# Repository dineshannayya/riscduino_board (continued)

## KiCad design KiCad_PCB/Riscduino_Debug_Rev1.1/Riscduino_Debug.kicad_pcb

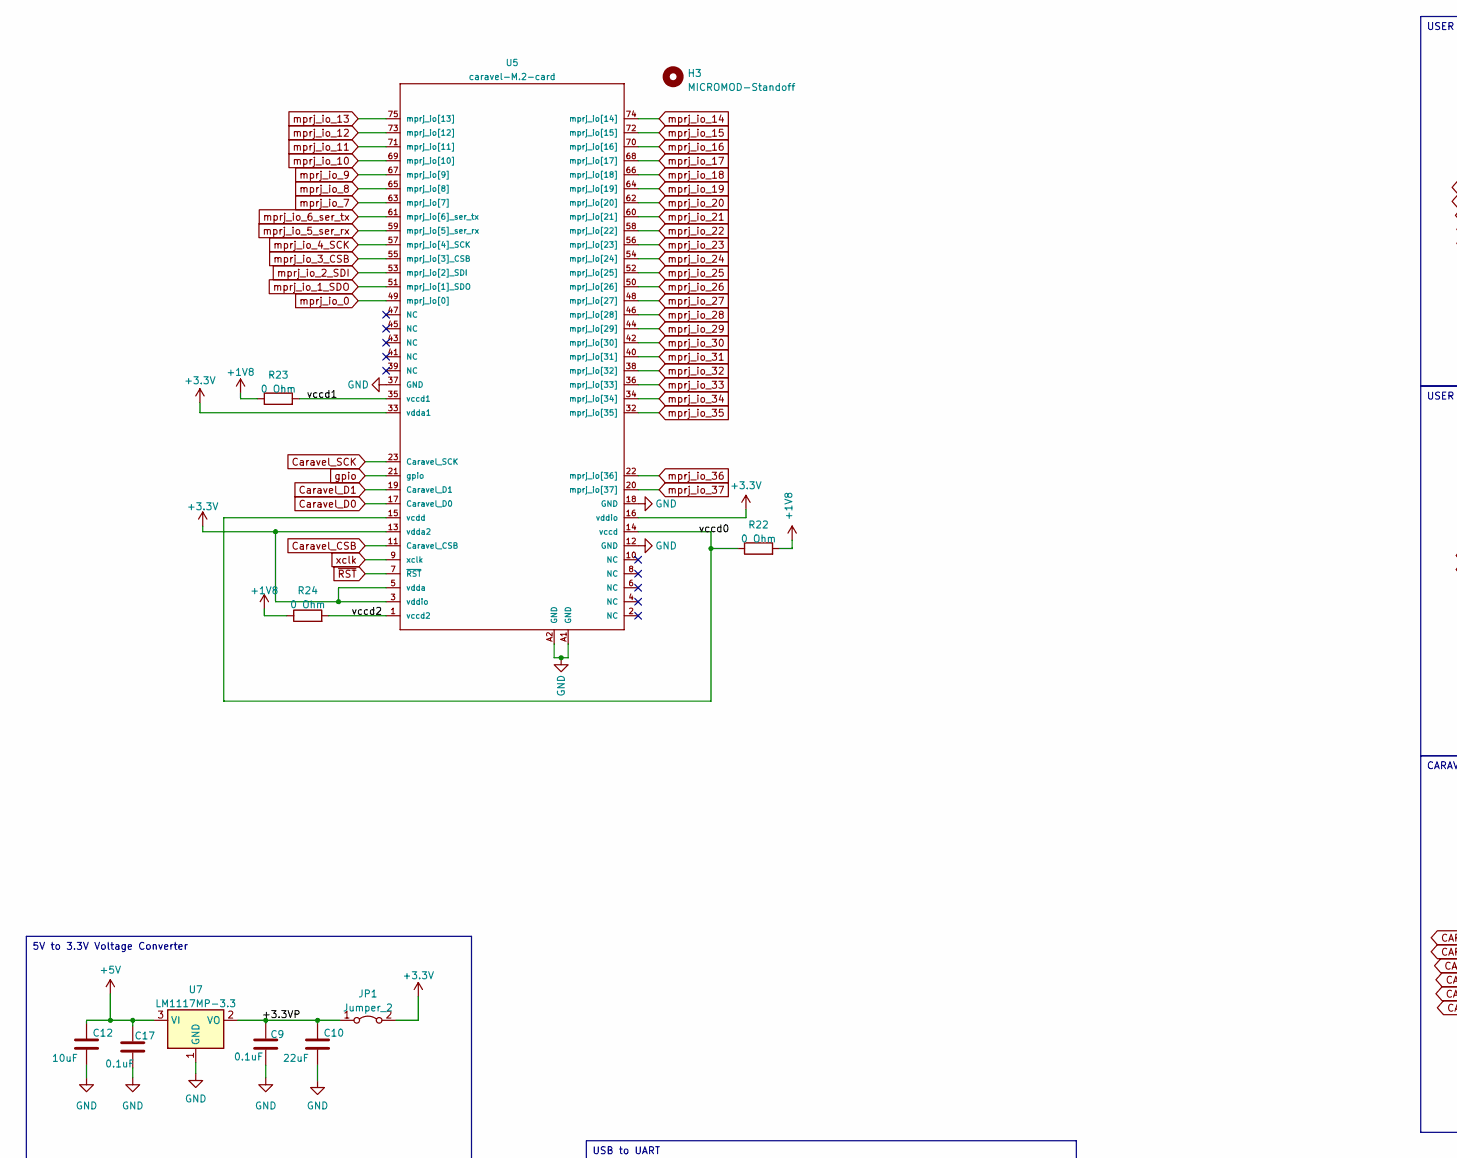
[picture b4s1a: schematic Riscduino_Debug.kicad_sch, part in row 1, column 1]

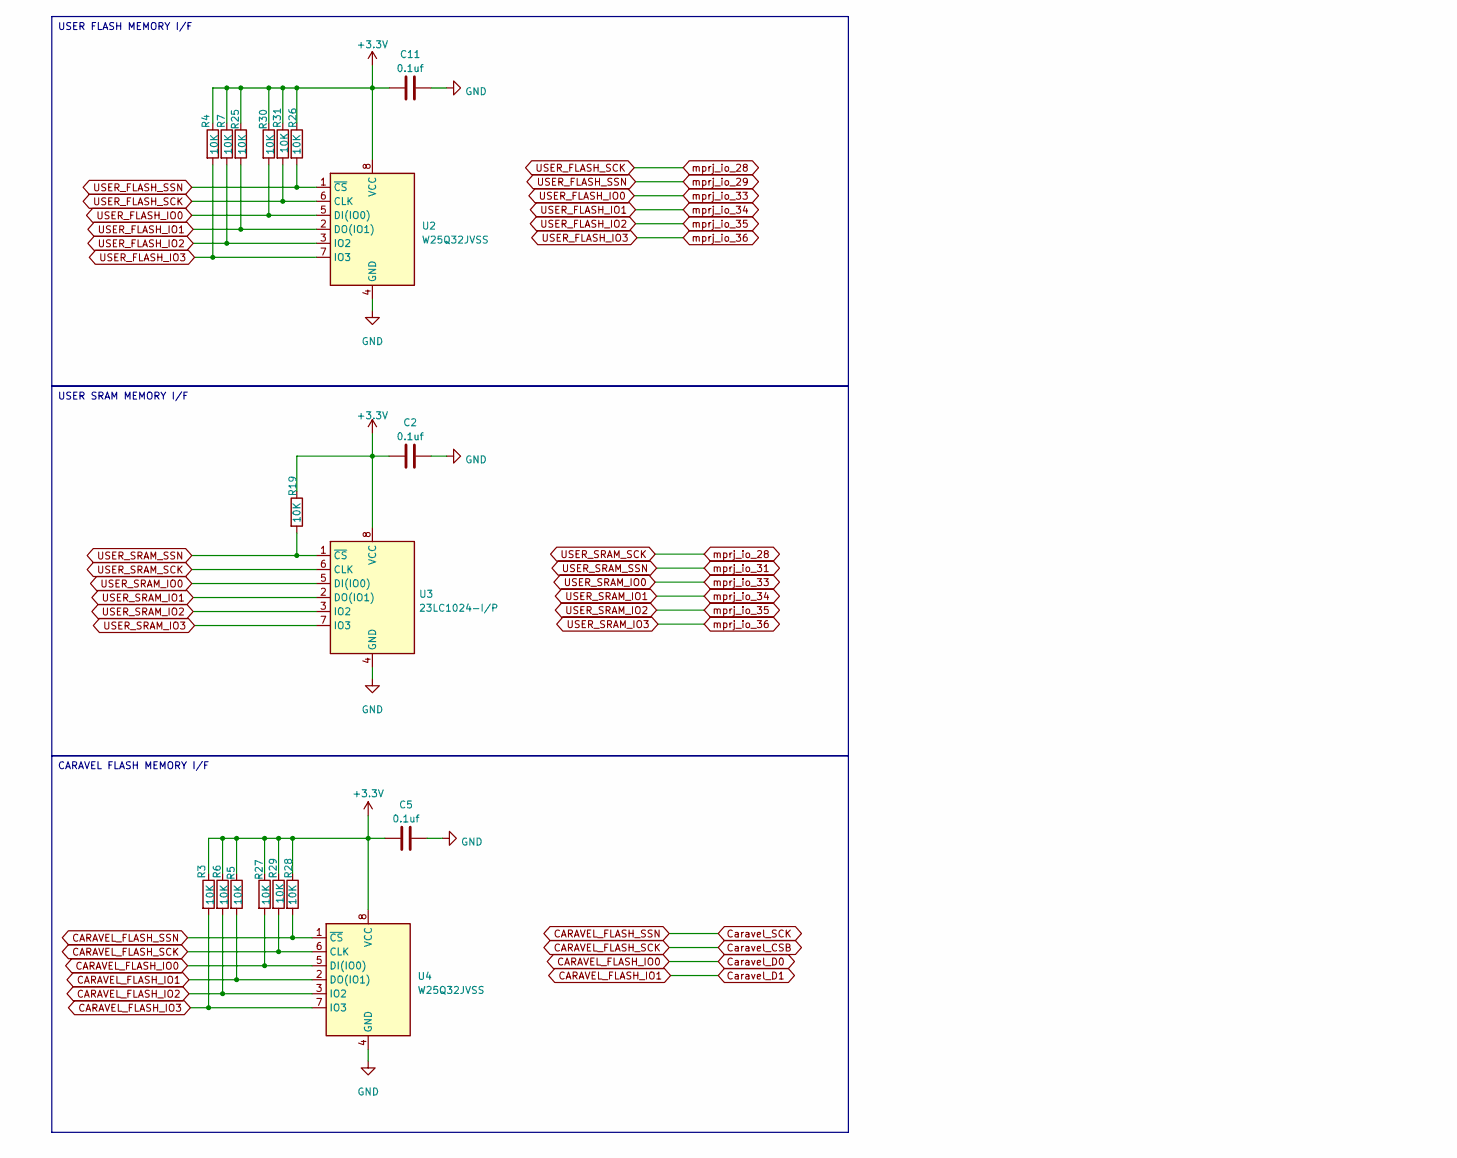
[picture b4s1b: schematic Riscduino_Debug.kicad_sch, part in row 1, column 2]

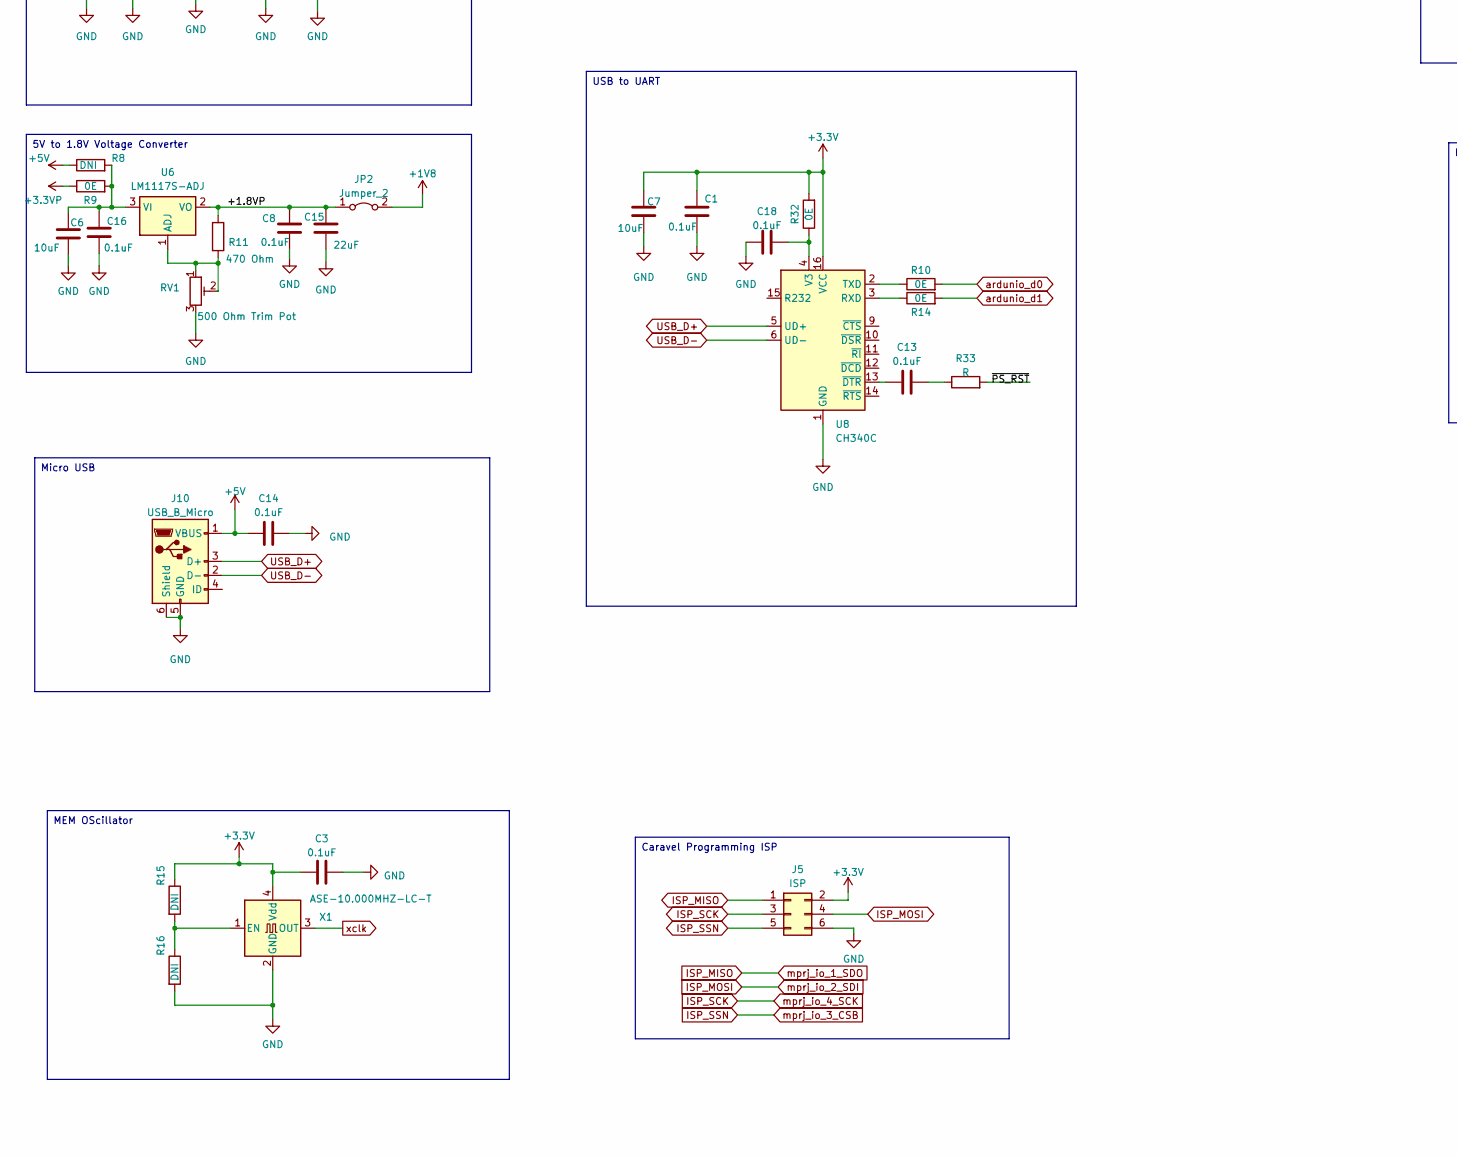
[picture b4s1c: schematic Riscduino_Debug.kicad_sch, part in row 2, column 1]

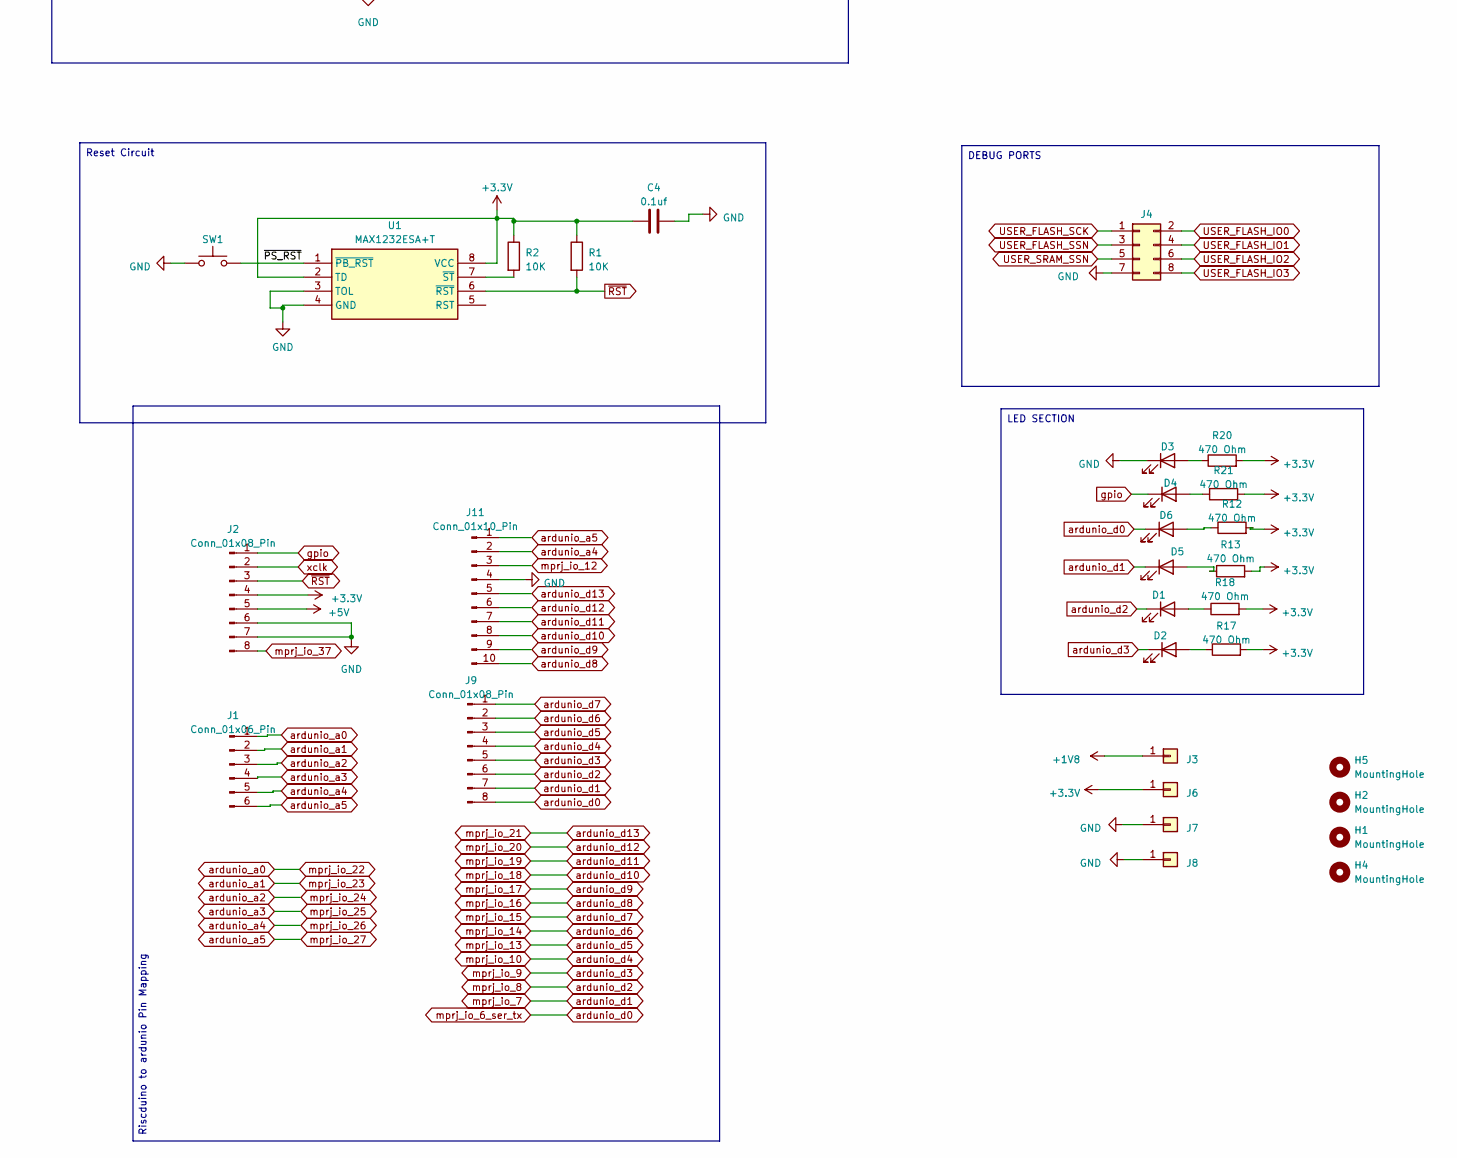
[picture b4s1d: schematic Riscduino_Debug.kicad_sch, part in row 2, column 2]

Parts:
C1, C3, C8, C9, C13, C14, C16, C17, C18: 0.1uF; C_0603_1608Metric_Pad1.08x0.95mm_HandSolder
C2, C4, C5, C11: 0.1uf; C_0603_1608Metric_Pad1.08x0.95mm_HandSolder
C6, C7, C12: 10uF; C_0805_2012Metric_Pad1.18x1.45mm_HandSolder
C10, C15: 22uF; C_0805_2012Metric_Pad1.18x1.45mm_HandSolder
D1, D2, D4, D5: GREEN LED; LED_0805_2012Metric_Pad1.15x1.40mm_HandSolder
D3: RED LED; LED_0805_2012Metric_Pad1.15x1.40mm_HandSolder
D6: BLUE LED; LED_0805_2012Metric_Pad1.15x1.40mm_HandSolder
H1, H2, H4, H5: MountingHole; MountingHole_3.2mm_M3
H3: MICROMOD-Standoff; MicroMod-Standoff
J1: Conn_01x06_Pin; PinHeader_1x06_P2.54mm_Vertical
J2, J9: Conn_01x08_Pin; PinHeader_1x08_P2.54mm_Vertical
J3, J6, J7, J8: Conn_01x01; PinHeader_1x01_P2.54mm_Vertical
J4: Conn_02x04_Odd_Even; PinHeader_2x04_P2.54mm_Vertical
J5: ISP; PinHeader_2x03_P2.54mm_Vertical
J10: USB_B_Micro; USB_Micro-B_Molex-105017-0001
J11: Conn_01x10_Pin; PinHeader_1x10_P2.54mm_Vertical
JP1, JP2: Jumper_2; PinHeader_1x02_P2.54mm_Vertical
R1, R2, R3, R4, R5, R6, R7, R19, R25, R26, R27, R28, R29, R30, R31: 10K; R_0603_1608Metric_Pad0.98x0.95mm_HandSolder
R8, R15, R16: DNI; R_0603_1608Metric_Pad0.98x0.95mm_HandSolder
R9, R10, R14, R32: 0E; R_0603_1608Metric_Pad0.98x0.95mm_HandSolder
R11, R12, R13, R17, R18, R20, R21: 470 Ohm; R_0603_1608Metric_Pad0.98x0.95mm_HandSolder
R22, R23, R24: 0 Ohm; R_0603_1608Metric_Pad0.98x0.95mm_HandSolder
R33: R; R_0603_1608Metric_Pad0.98x0.95mm_HandSolder
RV1: 500 Ohm Trim Pot; Potentiometer_Bourns_3296W_Vertical
SW1: 4Pin Round Button SPST Straight Tactile Switch SM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; SW_SPST_EVPBF_TS4550TP
U1: MAX1232ESA+T; SOIC-8-1EP_3.9x4.9mm_P1.27mm_EP2.29x3mm; Manufacturer_Part_Number MAX1232ESA+T; Mouser Part Number 700-MAX1232ESAT
U2, U4: W25Q32JVSS; SOIC-8_5.23x5.23mm_P1.27mm
U3: 23LC1024-I/P; DIP-8_W7.62mm_LongPads
U5: caravel-M.2-card; M.2-CONNECTOR-E
U6: LM1117S-ADJ; SOT-223-3_TabPin2
U7: LM1117MP-3.3; SOT-223-3_TabPin2
U8: CH340C; SOIC-16_3.9x9.9mm_P1.27mm
X1: ASE-10.000MHZ-LC-T; Crystal_SMD_Abracon_ABM8G-4Pin_3.2x2.5mm

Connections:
+1V8: J3.1, JP2.2 (B), R22.2, R23.1, R24.1
+3.3V: C1.1, C2.1, C3.1, C4.1, C5.1, C7.1, C11.1, J2.4, J5.2, J6.1, JP1.2 (B), R1.1, R2.1, R3.1, R4.1, R5.1, R6.1, R7.1, R12.2, R13.2, R15.1, R17.2, R18.2, R19.1, R20.2, R21.2, R25.1, R26.1, R27.1, R28.1, R29.1, R30.1, R31.1, R32.2, U1.2 (TD), U1.8 (VCC), U2.8 (VCC), U3.8 (VCC), U4.8 (VCC), U5.3 (vddio), U5.5 (vdda), U5.13 (vdda2), U5.16 (vddio), U5.33 (vdda1), U8.16 (VCC), X1.4 (Vdd)
+3.3VP: C9.1, C10.1, JP1.1 (A), R9.1, U7.2 (VO)
+5V: C12.1, C14.1, C17.1, J2.5, J10.1 (VBUS), R8.1, U7.3 (VI)
/+1.8VP: C8.1, C15.1, JP2.1 (A), R11.1, U6.2 (VO)
CARAVEL_FLASH_IO0: R27.2, U4.5 (DI(IO0)), U5.17 (Caravel_D0)
CARAVEL_FLASH_IO1: R5.2, U4.2 (DO(IO1)), U5.19 (Caravel_D1)
CARAVEL_FLASH_IO2: R6.2, U4.3 (IO2)
CARAVEL_FLASH_IO3: R3.2, U4.7 (IO3)
CARAVEL_FLASH_SCK: R29.2, U4.6 (CLK), U5.11 (Caravel_CSB)
CARAVEL_FLASH_SSN: R28.2, U4.1 (~CS), U5.23 (Caravel_SCK)
GND: C1.2, C2.2, C3.2, C4.2, C5.2, C6.2, C7.2, C8.2, C9.2, C10.2, C11.2, C12.2, C14.2, C15.2, C16.2, C17.2, C18.1, D3.1 (K), J2.6, J2.7, J4.7, J5.6, J7.1, J8.1, J10.5 (GND), J10.6 (Shield), J11.4, R16.2, RV1.3, SW1.1, U1.3 (TOL), U1.4 (GND), U2.4 (GND), U3.4 (GND), U4.4 (GND), U5.12 (GND), U5.18 (GND), U5.37 (GND), U5.A1 (GND), U5.A2 (GND), U7.1 (GND), U8.1 (GND), X1.2 (GND)
ISP_MISO: J5.1, U5.51 (mprj_io[1]_SDO)
ISP_MOSI: J5.4, U5.53 (mprj_io[2]_SDI)
ISP_SCK: J5.3, U5.57 (mprj_io[4]_SCK)
ISP_SSN: J5.5, U5.55 (mprj_io[3]_CSB)
unnamed: C13.2, R33.1
unnamed: D1.2 (A), R18.1
unnamed 18: D2.2 (A), R17.1; also elsewhere on the board
unnamed: D3.2 (A), R20.1
unnamed: D4.2 (A), R21.1
unnamed: D5.2 (A), R13.1
unnamed: D6.2 (A), R12.1
unnamed: SW1.2, U1.1 (~PB_RST)
unnamed: R2.2, U1.7 (~ST)
unnamed: R23.2, U5.35 (vccd1)
unnamed: R24.2, U5.1 (vccd2)
unnamed: R22.1, U5.14 (vccd), U5.15 (vcdd)
unnamed: R11.2, RV1.1, RV1.2, U6.1 (ADJ)
unnamed: C6.1, C16.1, R8.2, R9.2, U6.3 (VI)
unnamed: R14.1, U8.3 (RXD)
unnamed: R10.1, U8.2 (TXD)
unnamed: C18.2, R32.1, U8.4 (V3)
unnamed: C13.1, U8.13 (~DTR)
unnamed: R15.2, R16.1, X1.1 (EN)
USB_D+: J10.3 (D+), U8.5 (UD+)
USB_D-: J10.2 (D-), U8.6 (UD-)
USER_FLASH_IO0: J4.2, R30.2, U2.5 (DI(IO0)), U3.5 (DI(IO0)), U5.36 (mprj_io[33])
USER_FLASH_IO1: J4.4, R25.2, U2.2 (DO(IO1)), U3.2 (DO(IO1)), U5.34 (mprj_io[34])
USER_FLASH_IO2: J4.6, R7.2, U2.3 (IO2), U3.3 (IO2), U5.32 (mprj_io[35])
USER_FLASH_IO3: J4.8, R4.2, U2.7 (IO3), U3.7 (IO3), U5.22 (mprj_io[36])
USER_FLASH_SCK: J4.1, R31.2, U2.6 (CLK), U3.6 (CLK), U5.46 (mprj_io[28])
USER_FLASH_SSN: J4.3, R26.2, U2.1 (~CS), U5.44 (mprj_io[29])
USER_SRAM_SSN: J4.5, R19.2, U3.1 (~CS), U5.40 (mprj_io[31])
ardunio_a0: J1.1, U5.58 (mprj_io[22])
ardunio_a1: J1.2, U5.56 (mprj_io[23])
ardunio_a2: J1.3, U5.54 (mprj_io[24])
ardunio_a3: J1.4, U5.52 (mprj_io[25])
ardunio_a4: J1.5, J11.2, U5.50 (mprj_io[26])
ardunio_a5: J1.6, J11.1, U5.48 (mprj_io[27])
ardunio_d0: D6.1 (K), J9.8, R10.2, U5.61 (mprj_io[6]_ser_tx)
ardunio_d1: D5.1 (K), J9.7, R14.2, U5.63 (mprj_io[7])
ardunio_d2: D1.1 (K), J9.6, U5.65 (mprj_io[8])
ardunio_d3: D2.1 (K), J9.5, U5.67 (mprj_io[9]), U8.67; also elsewhere on the board
ardunio_d4: J9.4, U5.69 (mprj_io[10])
ardunio_d5: J9.3, U5.75 (mprj_io[13])
ardunio_d6: J9.2, U5.74 (mprj_io[14])
ardunio_d7: J9.1, U5.72 (mprj_io[15])
ardunio_d8: J11.10, U5.70 (mprj_io[16])
ardunio_d9: J11.9, U5.68 (mprj_io[17])
ardunio_d10: J11.8, U5.66 (mprj_io[18])
ardunio_d11: J11.7, U5.64 (mprj_io[19])
ardunio_d12: J11.6, U5.62 (mprj_io[20])
ardunio_d13: J11.5, U5.60 (mprj_io[21])
gpio: D4.1 (K), J2.1, U5.21 (gpio)
mprj_io_0: U5.49 (mprj_io[0])
mprj_io_5_ser_rx: U5.59 (mprj_io[5]_ser_rx)
mprj_io_11: U5.71 (mprj_io[11])
mprj_io_12: J11.3, U5.73 (mprj_io[12])
mprj_io_30: U5.42 (mprj_io[30])
mprj_io_32: U5.38 (mprj_io[32])
mprj_io_37: J2.8, U5.20 (mprj_io[37])
xclk: J2.2, U5.9 (xclk), X1.3 (OUT)
~RST: J2.3, R1.2, U1.6 (~RST), U5.7 (~RST)

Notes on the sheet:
MEM OScillator
5V to 3.3V Voltage Converter
LED SECTION
Riscduino to ardunio Pin Mapping
Micro USB
USB to UART
USER SRAM MEMORY I/F
DEBUG PORTS
Caravel Programming ISP
USER FLASH MEMORY I/F
5V to 1.8V Voltage Converter
Reset Circuit
CARAVEL FLASH MEMORY I/F

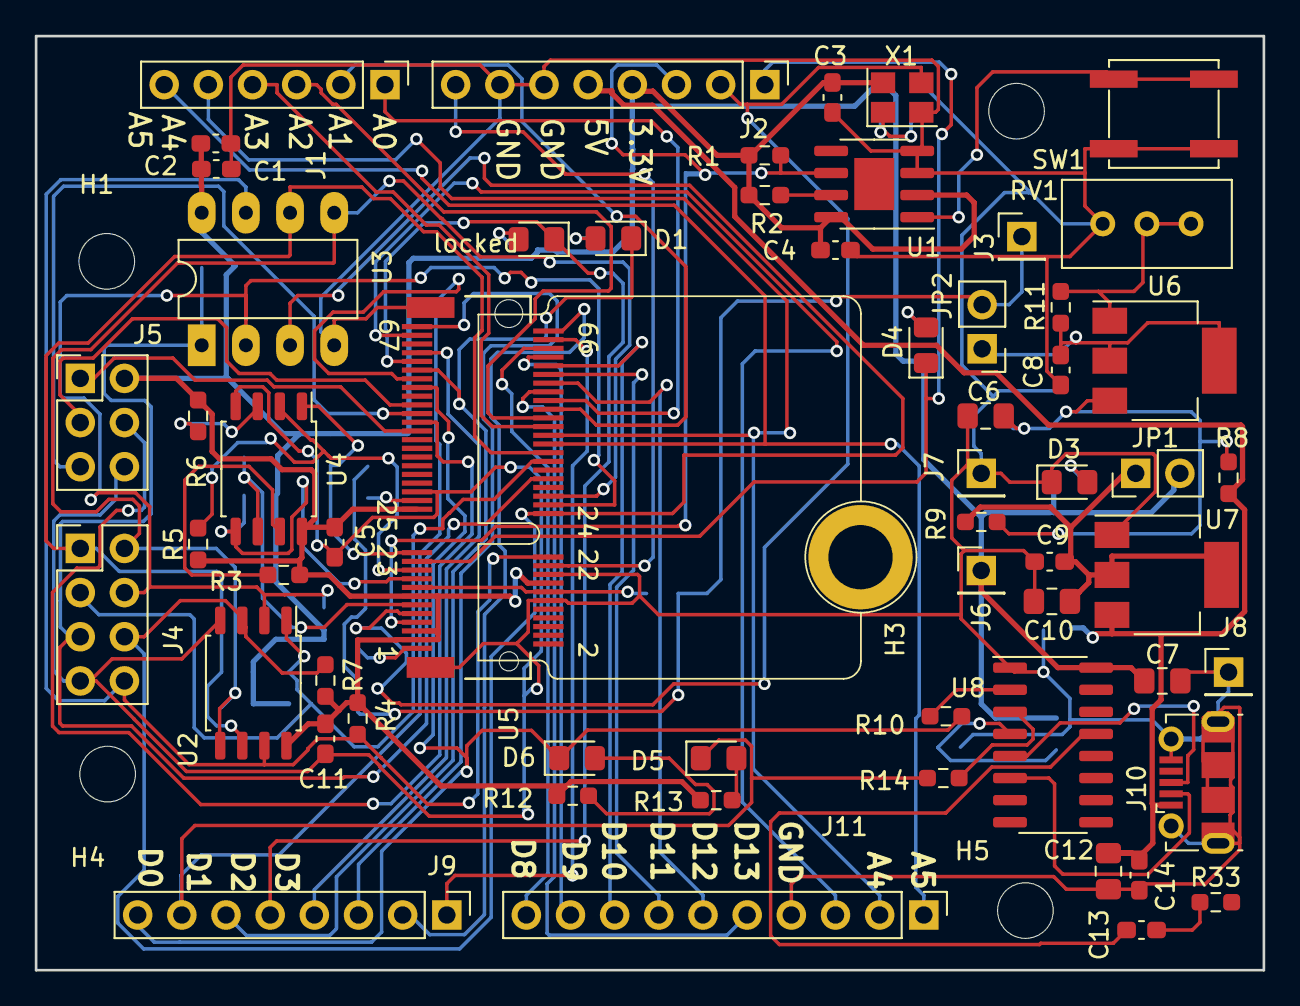
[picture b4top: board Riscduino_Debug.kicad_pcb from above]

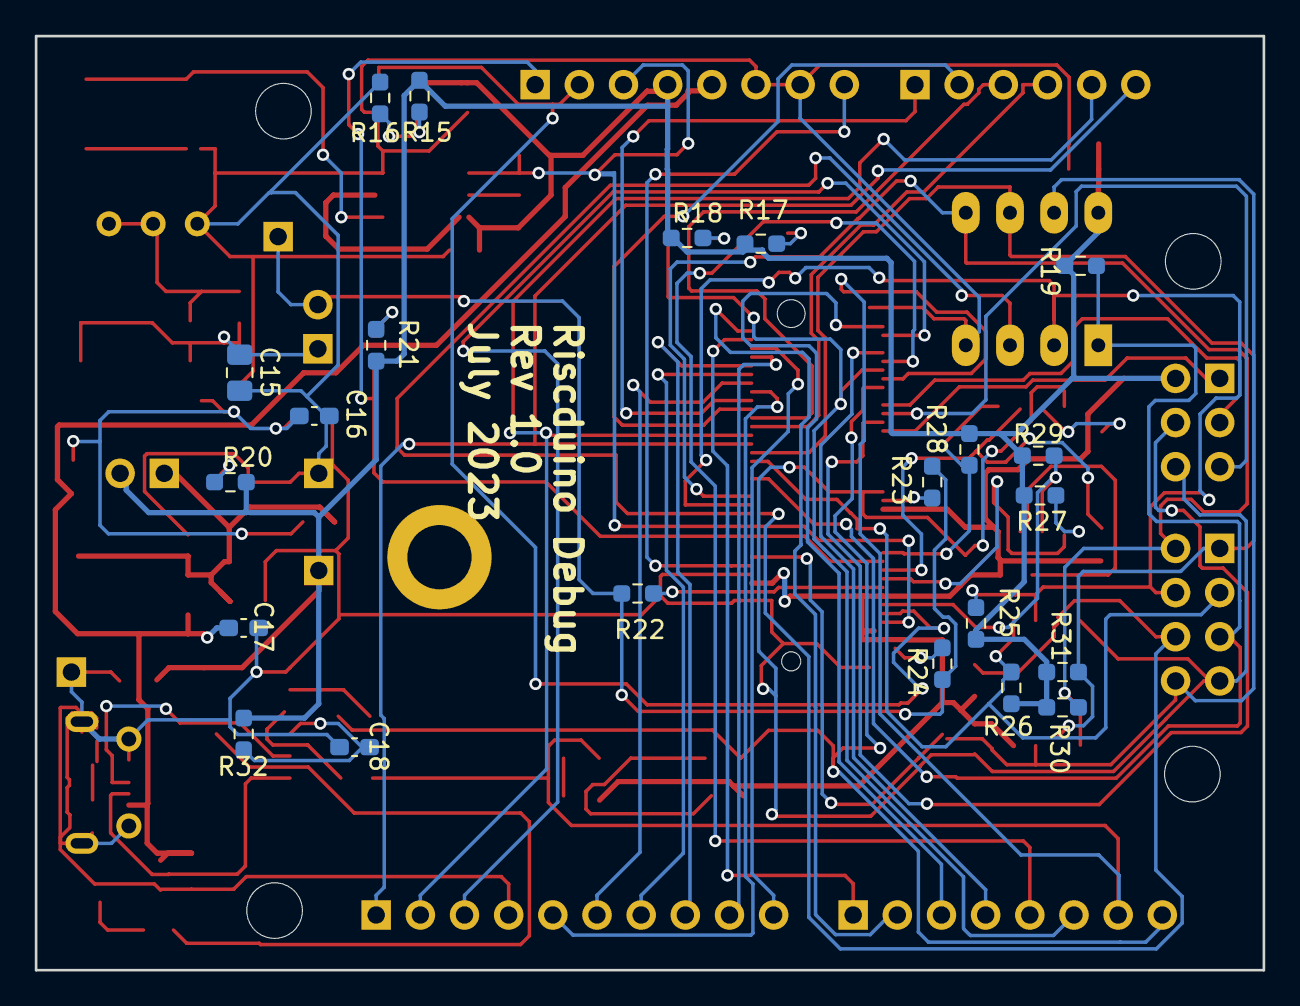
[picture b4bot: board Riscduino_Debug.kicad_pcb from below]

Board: 2 copper layers, 70.6 x 53.7 mm, 86 parts (22 on the bottom side), 69 nets.

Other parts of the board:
locked: GREEN LED; LED_0805_2012Metric_Pad1.15x1.40mm_HandSolder

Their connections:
unnamed 18: locked.2 (A); also elsewhere on the board
ardunio_d3: locked.1 (K); also elsewhere on the board

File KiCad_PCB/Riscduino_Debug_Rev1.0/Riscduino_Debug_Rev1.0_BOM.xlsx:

| Riscduino Debug Rev 1.0 BOM
Id | Designator | Footprint | Quantity | Designation | Supplier and ref | Column1 | _1
1 | J7,J8,J6,J3 | PinHeader_1x01_P2.54mm_Vertical | 4 | Conn_01x01
2 | JP1,JP2 | PinHeader_1x02_P2.54mm_Vertical | 2 | Jumper_2
3 | J2,J9 | PinHeader_1x08_P2.54mm_Vertical | 2 | Conn_01x08_Pin
4 | J11 | PinHeader_1x10_P2.54mm_Vertical | 1 | Conn_01x10_Pin
5 | J1 | PinHeader_1x06_P2.54mm_Vertical | 1 | Conn_01x06_Pin
6 | TP1 | PinHeader_1x01_P2.54mm_Vertical | 1 | TestPoint
7 | J4 | PinHeader_2x04_P2.54mm_Vertical | 1 | Conn_02x04_Odd_Even
8 | J10 | USB_Micro-B_Molex-105017-0001 | 1 | USB_B_Micro
9 | J5 | PinHeader_2x03_P2.54mm_Vertical | 1 | ISP
10 | R2,R1,R5,R6,R3,R4,R7,R25,R26,R27,R28,R29,R30,R31,R19 | R_0603_1608Metric_Pad0.98x0.95mm_HandSolder | 15 | 10K
2 | R12,R13,R11,R20,R17,R18,R21 | R_0603_1608Metric_Pad0.98x0.95mm_HandSolder | 7 | 470 Ohm
3 | R14,R9,R10,R32, R23,R24,R22 | R_0603_1608Metric_Pad0.98x0.95mm_HandSolder | 7 | 0E
4 | C3,C14,C8,C1,C13,C9,C18,C16,C17 C11,C4,C5,C2 | C_0603_1608Metric_Pad1.08x0.95mm_HandSolder | 13 | 0.1uF
5 | C10,C15 | C_0805_2012Metric_Pad1.18x1.45mm_HandSolder | 2 | 22uF
6 | C7,C12 | C_0805_2012Metric_Pad1.18x1.45mm_HandSolder | 2 | 10uF
7 | D3 | LED_0805_2012Metric_Pad1.15x1.40mm_HandSolder | 1 | RED LED
8 | D1,D2,D4,D5 | LED_0805_2012Metric_Pad1.15x1.40mm_HandSolder | 4 | GREEN LED
9 | D6 | LED_0805_2012Metric_Pad1.15x1.40mm_HandSolder | 1 | BLUE LED
10 | U7 | SOT-223-3_TabPin2 | 1 | LM1117MP-3.3
11 | U2,U4 | SOIC-8_5.23x5.23mm_P1.27mm | 2 | W25Q32JVSS
12 | U6 | SOT-223-3_TabPin2 | 1 | LM1117S-ADJ
13 | U8 | SOIC-16_3.9x9.9mm_P1.27mm | 1 | CH340C
14 | U1 | SOIC-8-1EP_3.9x4.9mm_P1.27mm_EP2.29x3mm | 1 | MAX1232ESA+T
15 | U3 | DIP-8_W7.62mm_LongPads | 1 | 23LC1024-I/P
16 | U5 | M.2-CONNECTOR-E | 1 | caravel-M.2-card
17 | SW1 | SW_SPST_EVPBF_TS4550TP | 1 | 4Pin Round Button SPST Straight Tactile Switch SMD - TS4550TP
18 | X1 | Crystal_SMD_Abracon_ABM8G-4Pin_3.2x2.5mm | 1 | ASE-10.000MHZ-LC-T
19 | RV1 | Potentiometer_Bourns_3296W_Vertical | 1 | 500 Ohm Trim Pot
 | Below componets are not used
1 | R8,R15,R16 | R_0603_1608Metric_Pad0.98x0.95mm_HandSolder | 3 | DNI | No Mounting
2 | H5,H4,H2,H1 | MountingHole_3.2mm_M3 | 4 | MountingHole | No Mounting
3 | C6 | SW_SPST_CK_KXT3 | 1 | 10uF | No Mounting
4 | H3 | MicroMod-Standoff | 1 | MICROMOD-Standoff | This mounting part of U5 Connector
